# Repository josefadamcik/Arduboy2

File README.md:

# SLIMBOY_SPI - Arduboy2 port to Arduino Nano and SPI display

This is a port of the [original Arduboy2 code](https://github.com/MLXXXp/Arduboy2) to the simpler and cheaper Arduino Nano and a SPI display and is based on [SLIMBOY - port for Arduino Nano and I²C display](https://github.com/harbaum/Arduboy2)  with slighlty different pinout.

TODO: Document PIN connections, image + describtion

The SLIMBOY_SPI setup has a few limitations over the original solution:

 - Uses only one speaker PIN
 - There is no RGB diode (yet)
 - The Atmega328 on the Arduino Nano has some limitations over the  Atmega32u4 of the original Arduboy
   - It has fewer timers and thus some custom sound libraries won't work 100%
   - It has 500 bytes less ram
   - It has less PWM pins and thus the green LED cannot be dimmed

These limitations only have a very minor impact on the usability and games like ShadowRunner just run fine on the SLIMBOY.

## Related

Several sound libraries exist for the Arduboy. Some of them have also
been ported the the Nano:

 - Matching port of [ArduboyTones](https://github.com/harbaum/ArduboyTones) - for use with SLIMBOY_SPI comentout `#define TONES_2_SPEAKER_PINS` and `#define TONES_VOLUME_CONTROL` (or use [a fork with those changes included](https://github.com/harbaum/ArduboyTones))
 - Matching port of [ATMlib](https://github.com/harbaum/ATMlib) - TODO check support and functionality with SLIMBOY_SPI

## Games tested on the Arduino Nano

 - ArduBreakout
 - Shadow-Runner
 - VIRUS-LQP-79
 - Pinball
 - Nineteen43

# Arduboy2 Library

The Arduboy2 library is maintained in a git repository hosted on [GitHub](https://github.com/) at:

https://github.com/MLXXXp/Arduboy2

The **Arduboy2** library is a fork of the [Arduboy library](https://github.com/Arduboy/Arduboy), which provides a standard *application programming interface* (API) to the display, buttons and other hardware of the Arduino based [Arduboy miniature game system](https://www.arduboy.com/).

The name *Arduboy2* doesn't indicate that it's for a new "next generation" of the Arduboy hardware. The name was changed so it can coexist in the Arduino IDE with the current *Arduboy* library, without conflict. This way, existing sketches can continue to use the *Arduboy* library and class, without changes, while new sketches can be written (or old ones modified) to use and take advantage of the capabilities of the *Arduboy2* class and library.

For notes on the differences between the *Arduboy2* library and the original *Arduboy* library, and for information on migrating a sketch currently using the *Arduboy* library, see the sections at the end of this document.

## Library documentation

Comments in the library header files are formatted for the [Doxygen](http://www.doxygen.org) document generation system. The HTML files generated using the configuration file _extras/Doxyfile_ can be found at:

https://MLXXXp.github.io/documents/Arduino/libraries/Arduboy2/Doxygen/html/index.html

A generated PDF file can be found at:

https://MLXXXp.github.io/documents/Arduino/libraries/Arduboy2/Doxygen/pdf/Arduboy2.pdf

## Installation

The Arduboy2 library can be installed using the Arduino IDE Library Manager:

- In the Arduino IDE select from the menus: `Sketch > Include Library > Manage Libraries...`
- In the Library Manager *Filter your search...* field enter *arduboy2*.
- Click somewhere within the Arduboy2 entry.
- Click on the *Install* button.

For more library installation information see

[Installing Additional Arduino Libraries - Using the Library Manager](https://www.arduino.cc/en/Guide/Libraries#toc3)

## Start up features

The *begin()* function, used to initialize the library, includes features that are intended to be available to all sketches using the library (unless the sketch developer has chosen to disable one or more of them to free up some code space):

### The boot logo

At the start of the sketch, the **ARDUBOY** logo scrolls down from the top of the screen to the center.

The RGB LED lights red then green then blue while the logo is scrolling. (If your Arduboy is one of those that has the RGB LED installed incorrectly, then it will light blue then off then red). For users who do not wish to have the RGB LED flash during the boot logo sequence, a flag can be set in system EEPROM to have it remain off. The included *SetSystemEEPROM* example sketch can be used to set this flag.

A user settable *unit name* of up to 6 characters can be saved in system EEPROM memory. If set, this name will be briefly displayed at the bottom of the boot logo screen, after the logo stops scrolling down. This feature is only available if the *Arduboy2* class is used, not the *Arduboy2Base* class. This is because it requires the text display functions, which are only available in the *Arduboy2* class. A flag in system EEPROM controls whether or not the *unit name* is displayed on the boot logo screen, regardless of whether the *unit name* itself has been set. The included *SetSystemEEPROM* example sketch can be used to set both the *unit name* and this flag.

Once the logo display sequence completes, the sketch continues.

For developers who wish to quickly begin testing, or impatient users who want to go strait to playing their game, the boot logo sequence can be bypassed by holding the *RIGHT* button while powering up, and then releasing it. Alternatively, the *RIGHT* button can be pressed while the logo is scrolling down.

For users who wish to always disable the displaying of the boot logo sequence on boot up, a flag in system EEPROM is available for this. The included *SetSystemEEPROM* example sketch can be used to set this flag.

### "Flashlight" mode

If the *UP* button is pressed and held when the Arduboy is powered on, it enters *flashlight* mode. This turns the RGB LED fully on, and all the pixels of the screen are lit, resulting in a bright white light suitable as a small flashlight. (For an incorrect RGB LED, only the screen will light). To exit *flashlight* mode the Arduboy must be restarted.

*Flashlight* mode is also sometimes useful to allow uploading of new sketches, in case the sketch currently loaded uses a large amount of RAM which creates a bootloader problem.

### Audio mute control

Pressing and holding the *B* button when powering on will enter *System Control* mode. The RGB LED will light blue (red for an incorrect LED) to indicate that you are in *system control* mode. You must continue to hold the *B* button to remain in this mode. The only *system control* function currently implemented is *audio mute control*.

Pressing the *UP* button (while still holding *B*) will set a flag in system EEPROM indicating *audio enabled*. The RGB LED will flash green once (off for an incorrect LED) to indicate this action.

Pressing the *DOWN* button (while still holding *B*) will set the flag to *audio disabled* (muted). The RGB LED will flash red once (blue for an incorrect LED) to indicate this action.

Releasing the *B* button will exit *system control* mode and the sketch will continue.

Note that the audio control feature only sets a flag in EEPROM. Whatever code actually produces the sound must use the *audio.enabled()* function to check and honor the mute state. Audio libraries written with the Arduboy system in mind, such as the available *ArduboyPlaytune* and *ArduboyTones*, should do this. However, be aware that for some sketches, which don't use the Arduboy2 or other compliant library and generate sounds in their own way, this method of muting sound may not work.

## Using the library in a sketch

As with most libraries, to use Arduboy2 in your sketch you must include its header file at the start:

```cpp
#include <Arduboy2.h>
```

You must then create an Arduboy2 class object:

```cpp
Arduboy2 arduboy;
```

Naming the object *arduboy* has become somewhat of a standard, but you can use a different name if you wish.

To initialize the library, you must call its *begin()* function. This is usually done at the start of the sketch's *setup()* function:

```cpp
void setup()
{
  arduboy.begin();
  // more setup code follows, if required
}
```

The rest of the Arduboy2 functions will now be available for use.

If you wish to use the Sprites class functions you must create a Sprites object:

```cpp
Sprites sprites;
```

Sample sketches have been included with the library as examples of how to use it. To load an example, for examination and uploading to the Arduboy, using the Arduino IDE menus select:

`File > Examples > Arduboy2`

More information on writing sketches for the Arduboy can be found in the [Arduboy Community Forum](http://community.arduboy.com/).

### Using EEPROM in a sketch

The Arduboy2 library reserves an area at the start of EEPROM for storing system information, such as the current audio mute state and the Unit Name and Unit ID. A sketch **must not** use this reserved area for its own purposes. A sketch may use any EEPROM past this reserved area. The first EEPROM address available for sketch use is given as the defined value *EEPROM_STORAGE_SPACE_START*

### Audio control functions

The library includes an Arduboy2Audio class. This class provides functions to enable and disable (mute) sound and also save the current mute state so that it remains in effect over power cycles and after loading a different sketch. It doesn't contain anything to actually produce sound.

The Arduboy2Base class, and thus the Arduboy2 class, creates an Arduboy2Audio class object named *audio*, so a sketch doesn't need to create its own Arduboy2Audio object.

Example:

```cpp
#include <Arduboy2.h>

Arduboy2 arduboy;

// Arduboy2Audio functions can be called as follows:
  arduboy.audio.on();
  arduboy.audio.off();
```

### Simple tone generation

The *BeepPin1* and *BeepPin2* classes are available to generate simple square wave tones using speaker pin 1 and speaker pin 2 respectively. These classes are documented in file *Arduboy2Beep.h*. Also, *BeepDemo* is included as one of the example sketches, which demonstrates basic use.

NOTE: These functions will not work with a DevKit Arduboy because the speaker pins used cannot be directly controlled by a timer/counter. "Dummy" functions are provided so a sketch will compile and work properly but no sound will be produced.

### Ways to make more code space available to sketches

#### Sound effects and music

If all you want is to play single tones, using the built in *BeepPin1* or *BeepPin2* classes will be very efficient.

If you want to be able to play sequences of tones or background music, using the [*ArduboyTones*](https://github.com/MLXXXp/ArduboyTones) library will be more code efficient than using [*ArduboyPlaytune*](https://github.com/Arduboy/ArduboyPlayTune) or most other sound libraries compatible with the Arduboy. *ArduboyTones* even produces less code than the [Arduino built in *tone()* function](https://www.arduino.cc/en/Reference/Tone). You'll have to decide on the appropriate library or functions you use to generate sound, based on the features required and how much memory you want it to use.

#### Remove the text functions

If your sketch doesn't use any of the functions for displaying text, such as *setCursor()* and *print()*, you can remove them. You could do this if your sketch generates whatever text it requires by some other means. Removing the text functions frees up code by not including the font table and some code that is always pulled in by inheriting the [Arduino *Print* class](http://playground.arduino.cc/Code/Printclass).

To eliminate text capability in your sketch, when creating the library object simply use the *Arduboy2Base* class instead of *Arduboy2*:

For example, if the object will be named *arduboy*:

Replace

```cpp
Arduboy2 arduboy;
```

with

```cpp
Arduboy2Base arduboy;
```

#### Remove boot up features

As previously described, the *begin()* function includes features that are intended to be available to all sketches during boot up. However, if you're looking to gain some code space, you can call *boot()* instead of *begin()*. This will initialize the system but not include any of the extra boot up features. If desired, you can then add back in any of these features by calling the functions that perform them. You will have to trade off between the desirability of having a feature and how much memory you can recover by not including it.

A good way to use *boot()* instead of *begin()* is to copy the code from the body of the *begin()* function, in file *Arduboy2.cpp*, into your sketch and then edit it to retain the *boot()* call and any feature calls desired.

As of this writing, the begin function is:

```cpp
void Arduboy2Base::begin()
{
  boot(); // raw hardware

  display(); // blank the display (sBuffer is global, so cleared automatically)

  flashlight(); // light the RGB LED and screen if UP button is being held.

  // check for and handle buttons held during start up for system control
  systemButtons();

  audio.begin();

  bootLogo();

  waitNoButtons(); // wait for all buttons to be released
}
```

To incorporate it into your sketch just keep *boot()* and whatever feature calls are desired, if any. Comment out or delete the rest. Remember to add the class object name in front of each function call, since they're now being called from outside the class itself. If your sketch uses sound, it's a good idea to keep the call to *audio.begin()*.

For example: Let's say a sketch has its own code to enable, disable and save the *audio on/off* setting, and wants to keep the *flashlight* function. In *setup()* it could replace *begin()* with:

```cpp
  arduboy.boot(); // raw hardware

// *** This particular sketch clears the display soon, so it doesn't need this:
//  display(); // blank the display (sBuffer is global, so cleared automatically)

  arduboy.flashlight(); // light the RGB LED and screen if UP button is being held.

  // check for and handle buttons held during start up for system control
//  systemButtons();

  arduboy.audio.begin();

//  bootLogo();

//  waitNoButtons(); // wait for all buttons to be released
```

This saves whatever code *display()*, *systemButtons()*, *bootLogo()* and *waitNoButtons()* would use.

There are a few functions provided that are roughly equivalent to the standard functions used by *begin()* but which use less code space.

- *bootLogoCompressed()*, *bootLogoSpritesSelfMasked()*, *bootLogoSpritesOverwrite()*, *bootLogoSpritesBSelfMasked()* and *bootLogoSpritesBOverwrite()* will do the same as *bootLogo()* but will use *drawCompressed()*, or *Sprites* / *SpritesB* class *drawSelfMasked()* or *drawOverwrite()* functions respectively, instead of *drawBitmask()*, to render the logo. If the sketch uses one of these functions, then using the boot logo function that also uses it may reduce code size. It's best to try each of them to see which one produces the smallest size.
- *bootLogoText()* can be used in place *bootLogo()* in the case where the sketch uses text functions. It renders the logo as text instead of as a bitmap (so doesn't look as good).
- *safeMode()* can be used in place of *flashlight()* for cases where it's needed to allow uploading a new sketch when the bootloader "magic key" problem is an issue. It only lights the red RGB LED, so you don't get the bright light that is the primary purpose of *flashlight()*.

#### Use the SpritesB class instead of Sprites

The *SpritesB* class has functions identical to the *Sprites* class. The difference is that *SpritesB* is optimized for small code size rather than execution speed. If you want to use the sprites functions, and the slower speed of *SpritesB* doesn't affect your sketch, you may be able to use it to gain some code space.

Even if the speed is acceptable when using *SpritesB*, you should still try using *Sprites*. In some cases *Sprites* will produce less code than *SpritesB*, notably when only one of the functions is used.

You can easily switch between using *Sprites* or *SpritesB* by using one or the other to create an object instance:

```cpp
Sprites sprites;  // Use this to optimize for execution speed
SpritesB sprites; // Use this to (likely) optimize for code size
```

#### Eliminate the USB stack code

**Warning:** Although this will free up a fair amount of code and some RAM space, without an active USB interface uploader programs will be unable to automatically force a reset to invoke the bootloader. This means the user will have to manually initiate a reset in order to upload a new sketch. This can be an inconvenience or even frustrating for a user, due to the fact that timing the sequence can sometimes be tricky. Therefore, using this technique should be considered as a last resort. If it is used, the sketch documentation should state clearly what will be involved to upload a new sketch.

The *ARDUBOY_NO_USB* macro is used to eliminate the USB code. The *exitToBootloader()* function is available to make it easier for a user to invoke the bootloader. For more details, see the documentation provided for these.

----------

## What's different from Arduboy library V1.1

A main goal of Arduboy2 is to provide ways in which more code space can be freed for use by large sketches. Another goal is to allow methods other than the *tunes* functions to be used to produce sounds. Arduboy2 remains substantially compatible with [Arduboy library V1.1](https://github.com/Arduboy/Arduboy/releases/tag/v1.1), which was the latest stable release at the time of the fork. Arduboy2 is based on the code targeted for Arduboy library V1.2, which was still in development and unreleased at the time it was forked.

Main differences between Arduboy2 and Arduboy V1.1 are:

- The *ArduboyTunes* subclass, which provided the *tunes.xxx()* functions, has been removed. It's functionality is available in a separate [*ArduboyPlaytune* library](https://github.com/Arduboy/ArduboyPlayTune). By removing these functions, more code space may become available because interrupt routines and other support code was being compiled in even if a sketch didn't make use them. Another benefit is that without the automatic installation of timer interrupt service routines, other audio generating functions and libraries, that need access to the same interrupts, can now be used. Removal of the *tunes* functions is the main API incompatibility with Arduboy V1.1. Sketches written to use *tunes* functions will need some minor modifications in order to make them work with Arduboy2 plus ArduboyPlaytune, [ArduboyTones](https://github.com/MLXXXp/ArduboyTones), or some other audio library.
- Arduboy library V1.1 uses timer 1 for the *tunes* functions. This causes problems when attempting to control the Arduboy's RGB LED using PWM, such as with *setRGBled()*, because it also requires timer 1. Since the *tunes* functionality has been removed from Arduboy2, there are no problems with using the RGB LED (except those caused by the RGB LED being incorrectly installed). Of course, using an external library that uses timer 1, such as *ArduboyPlaytune*, may reintroduce the problems. However, using a library that doesn't use timer 1, such as *ArduboyTones*, is now an option.
- The code to generate text output, using *setCursor()*, *print()*, etc., can be removed to free up code space, if a sketch doesn't use any text functions. The *Arduboy2* class includes the text functions but using the *Arduboy2Base* class instead will eliminate them. With text functions included, the font table and some support functions are always compiled in even if not used. The API for using text functions is the same as Arduboy V1.1 with some additional functions added:
 - *setTextColor()* and *setTextBackground()* allow for printing black text on a white background.
 - *getCursorX()* and *getCursorY()* allow for determining the current text cursor position.
 - The *clear()* function will now reset the text cursor to home position 0, 0.
- A new feature has been added which allows the *audio on/off* flag in system EEPROM to be configured by the user when the sketch starts. The flag is used by the Arduboy and Arduboy2 *audio* subclass, along with external sound functions and libraries, to provide a standardized sound mute capability. See the information above, under the heading *Audio mute control*, for more details.
- The *color* parameter, which is the last parameter for most of the drawing functions, has been made optional and will default to WHITE if not included in the call. This doesn't save any code but has been added as a convenience, since most drawing functions are called with WHITE specified.
- A new function *digitalWriteRGB()* has been added to control the RGB LED digitally instead of using PWM. This uses less code if just turning the RGB LEDs fully on or off is all that's required.
- The *beginNoLogo()* function is not included. This function could be used in Arduboy V1.1 in place of *begin()* to suppress the displaying of the ARDUBOY logo and thus free up the code that it required. Instead, Arduboy2 allows a sketch to call *boot()* and then add in any extra features that *begin()* provides by calling their functions directly after *boot()*, if desired.
- The *ArduboyCore* and *ArduboyAudio* base classes, previously only available to, and used to derive, the *Arduboy* class, have been made publicly available for the benefit of developers who may wish to use them as the base of an entirely new library. This change doesn't affect the existing API.

As of version 2.1.0 functionality from the [Team A.R.G.](http://www.team-arg.org/) *Arglib* library has been added:

- The sprite drawing functions, collision detection functions, and button handling functions that Team A.R.G. incorporated from the [ArduboyExtra](https://github.com/yyyc514/ArduboyExtra) project. The *poll()* function was renamed *pollButtons()* for clarity. The *Sprites* class doesn't require a parameter for the constructor, whereas in *Arglib* a pointer to an Arduboy class object is required.
- The *drawCompressed()* function, which allows compressed bitmaps to be drawn. Saving bitmaps in compressed form may reduce overall sketch size.

Team A.R.G. has now migrated all of their games and demos to use the Arduboy2 library.

## Migrating a sketch from Arduboy library V1.1 to Arduboy2

Since the Arduboy2 library can coexist in the Arduino IDE alongside the Arduboy library V1.1, a currently working sketch that uses Arduboy V1.1 doesn't have to be migrated to Arduboy2. However, if you want to switch a sketch to Arduboy2 for further development, in order to take advantage of any of the changes and enhancements, it's generally relatively easy.

The Arduboy2 library, for the most part, is compatible with Arduboy library V1.1 but migrating a sketch to Arduboy2 will require some small changes, and more so if it uses the *tunes* functions, such as *tunes.tone()* or *tunes.playScore()*.

### Required changes

The first thing to do is change the `include` for the library header file:

```cpp
#include <Arduboy.h>
```

becomes

```cpp
#include <Arduboy2.h>
```

If it was "Arduboy.h" (in quotes), it's still better to change it to &lt;Arduboy2.h&gt; (in angle brackets).

The same thing has to be done with creating the library object. (If the object name isn't *arduboy*, keep whatever name is used.):

```cpp
Arduboy arduboy;
```

becomes

```cpp
Arduboy2 arduboy;
```

If the sketch doesn't use any *tunes* functions, there's a good chance this is all that has to be done to make it compile.

### Sketch uses only *tunes.tone()* for sound

If the sketch has sound but only uses *tunes.tone()*, solutions are:

#### Solution 1: Switch to using Arduino *tone()*

An easy change is to use the Arduino built in *tone()* function. You can add a function to the sketch that wraps *tone()* so that it works like *tunes.tone()*, like so:

```cpp
// Wrap the Arduino tone() function so that the pin doesn't have to be
// specified each time. Also, don't play if audio is set to off.
void playTone(unsigned int frequency, unsigned long duration)
{
  if (arduboy.audio.enabled() == true)
  {
    tone(PIN_SPEAKER_1, frequency, duration);
  }
}
```

You then change all *tunes.tone()* calls to *playTone()* calls using the same parameter values. For example:

```cpp
  arduboy.tunes.tone(1000, 250);
```

becomes

```cpp
  playTone(1000, 250);
```

#### Solution 2: Switch to using the ArduboyTones library

Changing to the *ArduboyTones* library is slightly more complicated. The advantage is that it will generate less code than using *tone()* and will also allow you to easily enhance the sketch to play tone sequences instead of just single tones. ArduboyTones can also play each tone at either normal or a higher volume.

You have to add an include for the ArduboyTones header file:

```cpp
#include <ArduboyTones.h>
```

You then have to create an object for the *ArduboyTones* class and pass it a pointer to the Arduboy2 *audio.enabled()* function. This must go after the creation of the Arduboy2 object, like so:

```cpp
Arduboy2 arduboy;
ArduboyTones sound(arduboy.audio.enabled);
```

You then change all Arduboy *tunes.tone()* calls to ArduboyTones *tone()* calls using the same parameter values. For example:

```cpp
  arduboy.tunes.tone(1000, 250);
```

becomes

```cpp
  sound.tone(1000, 250);
```

See the [ArduboyTones](https://github.com/MLXXXp/ArduboyTones) README file for more information on installing and using it.

#### Solution 3: Switch to using the ArduboyPlaytune library.

See the following for how to do this:

### Sketch uses *tunes.playScore()*

If the sketch uses *tunes.playScore()*, probably the easiest solution is to use the *ArduboyPlaytune* library. *ArduboyPlaytune* is essentially the code that was in the Arduboy V1.1 *tunes* subclass, which has been removed from Arduboy2. It's been cleaned up and a few enhancements have been added, but all the Arduboy V1.1 *tunes* functions are available.

You have to add an include for the ArduboyPlaytune header file:

```cpp
#include <ArduboyPlaytune.h>
```

You then have to create an object for the *ArduboyPlaytune* class and pass it a pointer to the Arduboy2 *audio.enabled()* function. This must go after the creation of the Arduboy2 object, like so:

```cpp
Arduboy2 arduboy;
ArduboyPlaytune tunes(arduboy.audio.enabled);
```

The sound channels must then be initialzed and assigned to the speaker pins. This code would go in the *setup()* function:

```cpp
  // audio setup
  tunes.initChannel(PIN_SPEAKER_1);
#ifndef AB_DEVKIT
  // if not a DevKit
  tunes.initChannel(PIN_SPEAKER_2);
#else
  // if it's a DevKit
  tunes.initChannel(PIN_SPEAKER_1); // use the same pin for both channels
  tunes.toneMutesScore(true);       // mute the score when a tone is sounding
#endif
```

If you name the ArduboyPlaytune object *tunes* as shown above, then you just have to remove the Arduboy object name from any *tunes* calls. For example:

```cpp
  arduboy.tunes.playScore(mySong);
```

becomes

```cpp
  tunes.playScore(mySong);
```

See the [*ArduboyPlaytune* library](https://github.com/Arduboy/ArduboyPlayTune) documentation for more information.

If you don't need to play scores containing two parts, and don't require tones to be played in parallel with a score that's playing, then as an alternative to using *ArduboyPlaytune* you may wish to consider switching to *ArduboyTones*. This may require a bit of work because any *ArduboyPlaytune* scores would have to be converted to *ArduboyTones* format. It would involve changing note numbers to frequencies. This could be simplified by using the provided *NOTE_* defines. Also, durations would have to be converted, including adding silent "rest" tones as necessary.

The benefit of using *ArduboyTones* would be reduced code size and possibly easier addition of new sequences without the need of a MIDI to Playtune format converter.

### Sketch uses the *beginNoLogo()* function instead of *begin()*

The *beginNoLogo()* function has been removed. Instead, *boot()* can be used with additional functions following it to add back in desired boot functionality. See the information above, under the heading *Remove boot up features*, for more details. Assuming the object is named *arduboy*, a direct replacement for *beginNoLogo()* would be:

```cpp
  arduboy.boot();
  arduboy.display();
  arduboy.flashlight();
  arduboy.audio.begin();
```

----------

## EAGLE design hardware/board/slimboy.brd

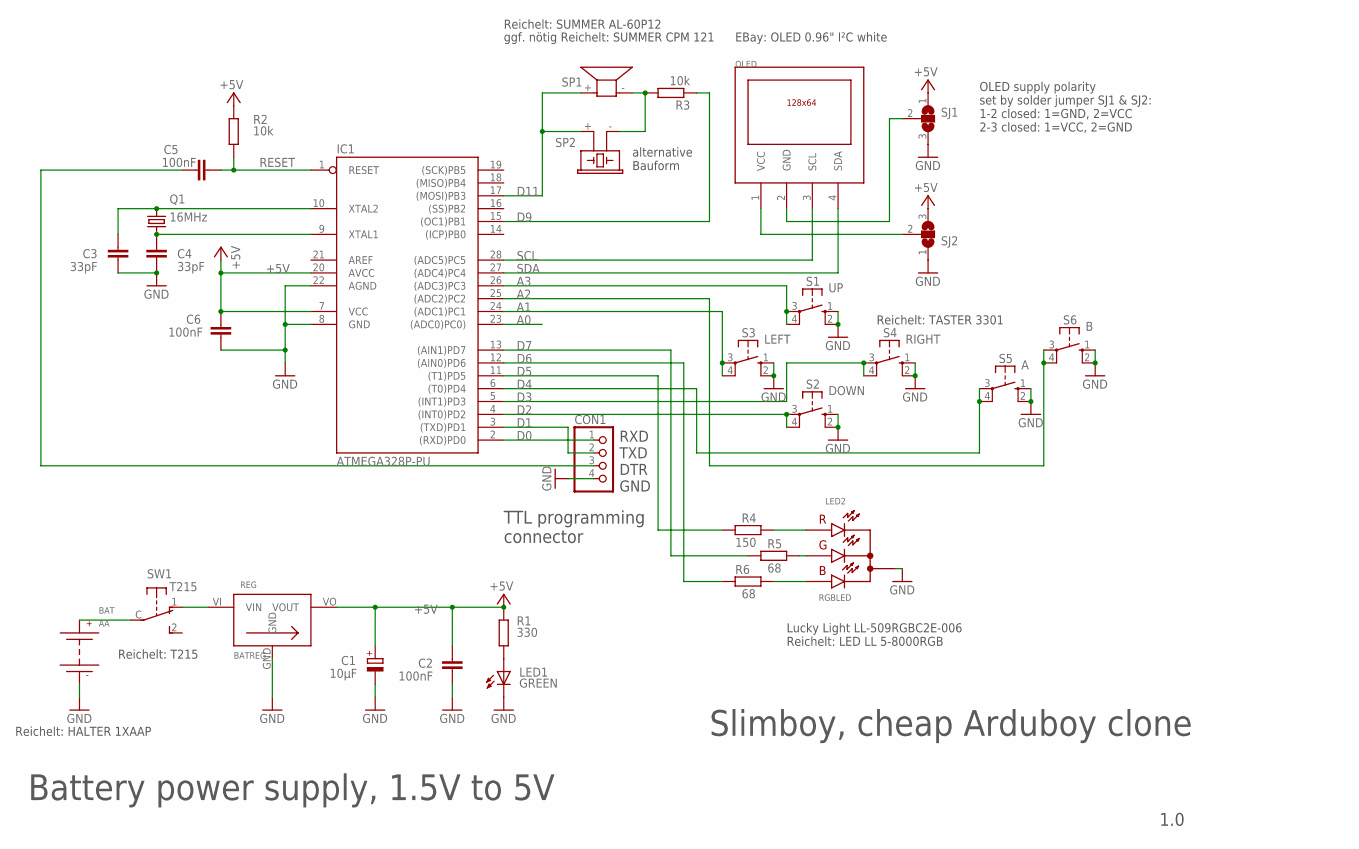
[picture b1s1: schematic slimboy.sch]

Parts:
BAT: AA; 1XAAP
C1: 10µF; TT2D5L
C2, C5, C6: 100nF; C050-025X075
C3, C4: 33pF; C025-025X050
CON1: PINHD-1X4/90; 1X04/90
IC1: ATMEGA328P-PU; DIL28-3
LED1: GREEN; LED3MM
LED2: RGBLED
OLED: OLED_0.96_I²C
Q1: 16MHz; HC49/S
R1: 330; 0204/7
R2, R3: 10k; 0204/7
R4: 150; 0204/7
R5, R6: 68; 0204/7
REG: BATREG
S1: UP; B3F-10XX
S2: DOWN; B3F-10XX
S3: LEFT; B3F-10XX
S4: RIGHT; B3F-10XX
S5: A; B3F-10XX
S6: B; B3F-10XX
SJ1, SJ2: SJ2W; SJ_2
SP1: KSS1201
SP2: F/CM12P
SW1: T215

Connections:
+5V: C1.+, C2.2, C6.2, IC1.7 (VCC), IC1.20 (AVCC), R1.1, R2.2, REG.VO (VOUT), SJ1.1, SJ2.3
A0: IC1.23 ((ADC0)PC0))
A1: IC1.24 ((ADC1)PC1), S3.3, S3.4 (P1)
A2: IC1.25 ((ADC2)PC2), S6.3, S6.4 (P1)
A3: IC1.26 ((ADC3)PC3), S1.3, S1.4 (P1)
D0: CON1.1, IC1.2 ((RXD)PD0)
D1: CON1.2, IC1.3 ((TXD)PD1)
D2: IC1.4 ((INT0)PD2), S2.3, S2.4 (P1)
D3: IC1.5 ((INT1)PD3), S4.3, S4.4 (P1)
D4: IC1.6 ((T0)PD4), S5.3, S5.4 (P1)
D5: IC1.11 ((T1)PD5), R4.2
D6: IC1.13 ((AIN1)PD7), R5.2
D7: IC1.12 ((AIN0)PD6), R6.2
D9: IC1.15 ((OC1)PB1), R3.1
D11: IC1.17 ((MOSI)PB3), SP1.+ (1), SP2.+ (1)
GND: BAT.-, C1.-, C2.1, C3.1, C4.1, C6.1, CON1.4, IC1.8 (GND), IC1.22 (AGND), LED1.K (C), LED2.GND (CAT), REG.GND, S1.1 (S), S1.2 (S1), S2.1 (S), S2.2 (S1), S3.1 (S), S3.2 (S1), S4.1 (S), S4.2 (S1), S5.1 (S), S5.2 (S1), S6.1 (S), S6.2 (S1), SJ1.3, SJ2.1
unnamed: C4.2, IC1.9 (XTAL1), Q1.1
unnamed: C3.2, IC1.10 (XTAL2), Q1.2
unnamed: LED1.A, R1.2
unnamed: REG.VI (VIN), SW1.1 (O)
unnamed: BAT.+, SW1.C
unnamed: LED2.R (AR), R4.1
unnamed: LED2.G (AG), R5.1
unnamed: R3.2, SP1.- (2), SP2.- (2)
unnamed: LED2.B (AB), R6.1
unnamed: C5.2, CON1.3
unnamed: OLED.2 (GND), SJ1.2
unnamed: OLED.1 (VCC), SJ2.2
RESET: C5.1, IC1.1 (RESET), R2.1
SCL: IC1.28 ((ADC5)PC5), OLED.3 (SCL)
SDA: IC1.27 ((ADC4)PC4), OLED.4 (SDA)

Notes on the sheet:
Reichelt: T215
Reichelt: HALTER 1XAAP
Lucky Light LL-509RGBC2E-006 Reichelt: LED LL 5-8000RGB
ggf. nötig Reichelt: SUMMER CPM 121
Reichelt: SUMMER AL-60P12
Reichelt: TASTER 3301
EBay: OLED 0.96" I²C white
Battery power supply, 1.5V to 5V
TTL programming connector
Slimboy, cheap Arduboy clone
1.0
RXD TXD DTR GND
alternative Bauform
OLED supply polarity set by solder jumper SJ1 & SJ2: 1-2 closed: 1=GND, 2=VCC 2-3 closed: 1=VCC, 2=GND

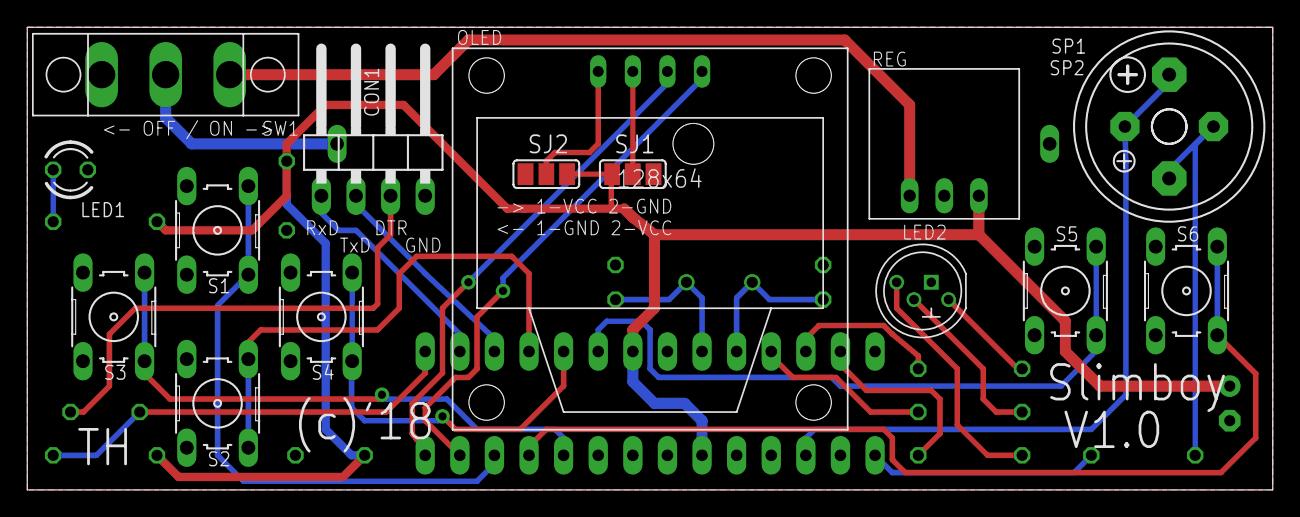
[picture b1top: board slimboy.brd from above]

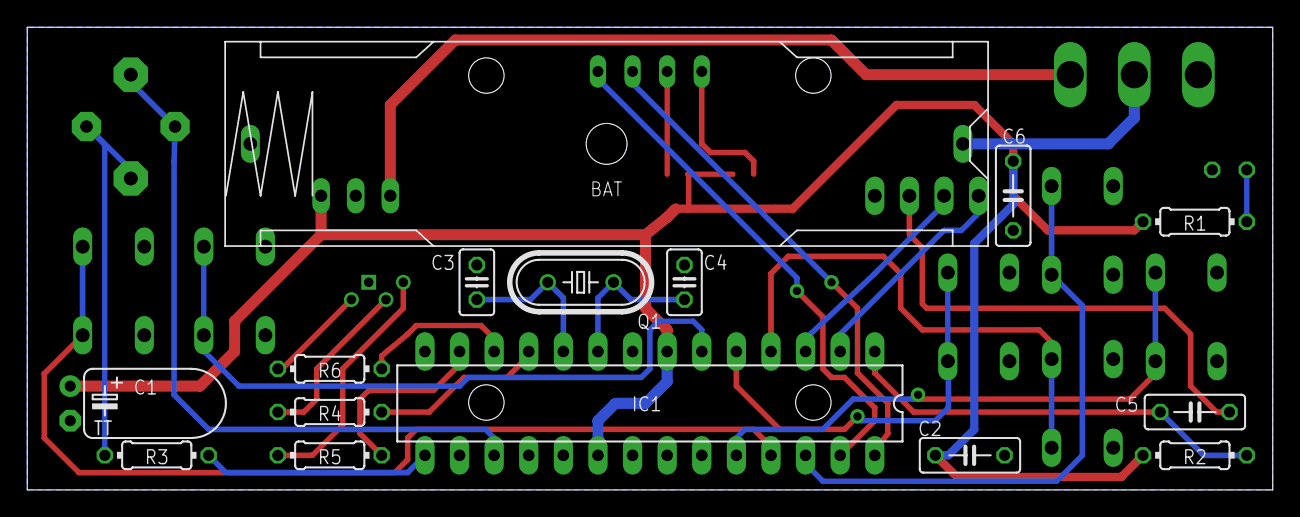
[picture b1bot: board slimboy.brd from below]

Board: 2 copper layers, 91.4 x 34.0 mm, 31 parts (15 on the bottom side), 30 nets.

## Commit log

2019-01-10 Added hardware information
2019-03-20 Change pinout
2019-03-20 Change pin initialization
2019-03-20 Remove i2c related code and return back to SPI
2019-03-23 Use different SPI pins, intialize them properly
2019-03-23 Use analog read for rnd seed
2019-03-23 Return speaker to pin 7, use only one speaker pin.
2019-03-24 Fix ArduBreakout to compile in PlatformIO (function declaration oredring)
2019-03-24 Fix BeepDemoand PlayTune examples
2019-03-24 Update README a bit
2019-03-24 Return back (uncomment) optimized parts in asm
2019-03-24 Fix link in README.md
